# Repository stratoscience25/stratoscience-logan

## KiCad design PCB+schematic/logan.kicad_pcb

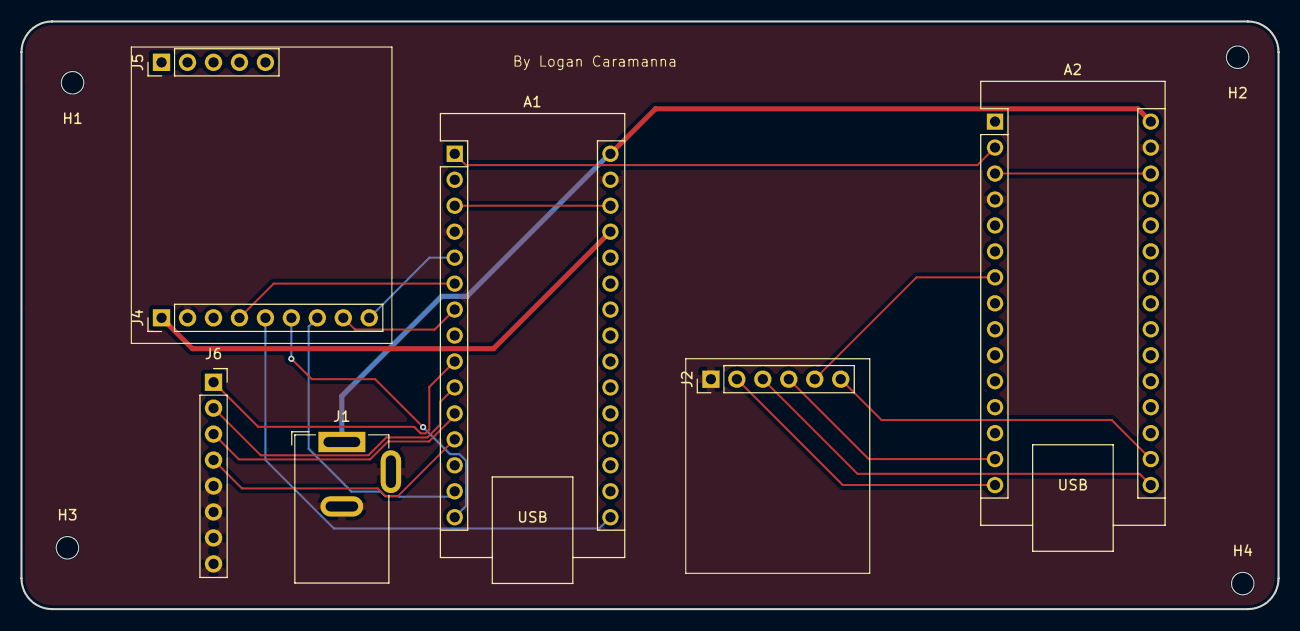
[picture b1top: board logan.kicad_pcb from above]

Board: 2 copper layers, 123.0 x 57.5 mm, 11 parts (0 on the bottom side), 21 nets.

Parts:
A1: Arduino Nano v3; Arduino_Nano
A2: Arduino_Nano_v3.x; Arduino_Nano
H1, H2, H3, H4: M2 Screwhole; MountingHole_2.2mm_M2
J1: Arduino DC Jack (6-12v); BarrelJack_GCT_DCJ200-10-A_Horizontal
J2: SD Card; PinHeader_1x06_P2.54mm_Vertical
J4: LoRa; PinHeader_1x09_P2.54mm_Vertical
J5: LoRa G pins; PinHeader_1x05_P2.54mm_Vertical
J6: Conn_01x08_Pin; PinSocket_1x08_P2.54mm_Vertical

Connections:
+5V: A1.27 (+5V), J4.1
/A0_TX: A1.1 (D1/TX), A2.2 (D0/RX)
/D6: A1.9 (D6), J6.1
/D7: A1.10 (D7), J6.2
/D8: A1.11 (D8), J6.3
/D9: A1.12 (D9), J6.4
/G0: A1.6 (D3), J4.4
/LORA_CS: A1.7 (D4), J4.8
/LORA_RST: A1.5 (D2), J4.9
/MISO: A1.15 (D12), J4.6
/MOSI: A1.14 (D11), J4.7
/NANO_VIN: A1.30 (VIN), A2.30 (VIN), J1.1
/SCK: A1.16 (D13), J4.5
/SD_CS: A2.7 (D4), J2.5
/SD_MISO: A2.15 (D12), J2.2
/SD_MOSI: A2.14 (D11), J2.4
/SD_SCK: A2.16 (D13), J2.3
/~A1_RESET: A2.3 (~RESET), A2.28 (~RESET)
/~RESET: A1.3 (~RESET), A1.28 (~RESET)
A1_3V3: A2.17 (3V3), J2.6
Earth: A1.4 (GND), A1.29 (GND), A2.4 (GND), A2.29 (GND), J1.2, J1.3, J2.1, J4.2, J6.5, J6.6, J6.7, J6.8

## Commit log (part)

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2025-12-06 New strato
2026-01-03 stuff
2026-01-03 test
2026-01-03 update files
2026-01-10 move main.ino into main/
2026-01-10 Update stuff
2026-01-10 LORAgit add *git add *git add *git add *
2026-01-10 LORAgit pushgit pushgit pushgit pushgit pushgit pushgit pushgit pushgit push
2026-02-07 Git usb works
2026-02-07 Loraaaaaaaaaa
2026-03-14 Update PCB
2026-05-09 Add gerbers, maybe
2026-06-06 LORA
2026-06-13 Long overdue folder structure update
